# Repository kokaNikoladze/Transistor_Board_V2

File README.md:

MIDI-CONTROLLED TRANSISTOR DRIVER
---------------------------------

This Arduino sketch turns MIDI messages into PWM voltage outputs to control transistors,
analog circuits, or other devices via 8 digital pins (pins 4–11).

FEATURES:
- Responds to USB MIDI Note On/Off: 
  - Note velocity controls output voltage (0–16383).
- Control Change (CC) support:
  - Channel 2: 7-bit control (0–127), scaled to 14-bit PWM.
  - Channel 1: High-resolution 14-bit NRPN-style control with exponential response.
    (MSB on CC < 64, LSB on CC >= 64)

PIN ASSIGNMENTS:
- Outputs 1–8 → Digital pins 4–11

NRPN FORMAT (FOR CHANNEL 1 HIGH-RES CONTROL):
- Input value: 0–16383
- MSB = value / 128     → Send to control #1 (or any CC < 64)
- LSB = value % 128     → Send to control #65 (or any CC >= 64)
- IMPORTANT: Send LSB first, then MSB

OTHER NOTES:
- Uses 14-bit PWM resolution
- PWM frequency set on pin 1 to 18.384kHz
- Includes exponential curve: pow(result / 16383.0, 3)
- Built for Teensy or other boards with analogWriteResolution()

DEPENDENCIES:
- usbMIDI library (Teensy compatible)

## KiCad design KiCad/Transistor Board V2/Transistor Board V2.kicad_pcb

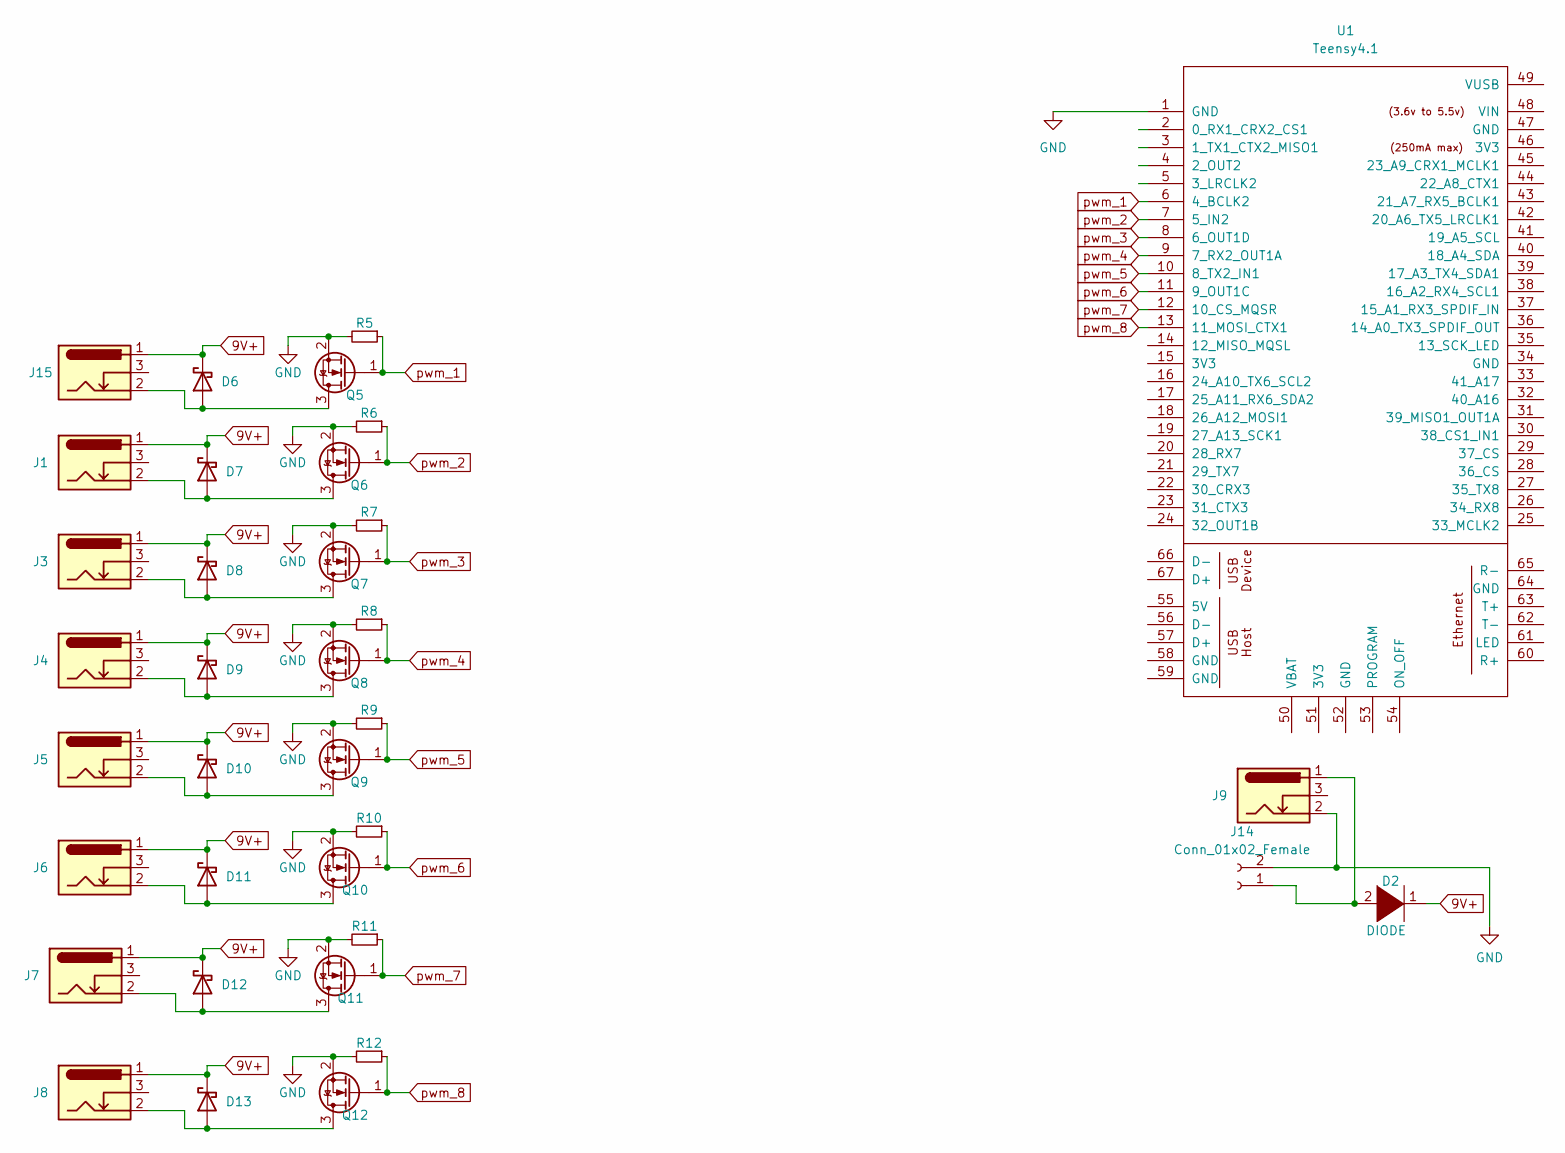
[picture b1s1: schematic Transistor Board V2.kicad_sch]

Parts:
D2: DIODE; TO-220-2_Horizontal_TabDown
D6, D7, D8, D9, D10, D11, D12, D13: SS54; D_SMA; LCSC C22452
J1, J3, J4, J5, J6, J7, J8, J9, J15: Barrel_Jack_Switch; DC-005-5A-2.0-SMT; LCSC C319134
J14: Conn_01x02_Female; PinHeader_1x02_P2.54mm_Vertical
Q5, Q6, Q7, Q8, Q9, Q10, Q11, Q12: AO3400A; SOT-23; LCSC C20917
R5, R6, R7, R8, R9, R10, R11, R12: R_Small; R_0805_2012Metric; LCSC C17414
U1: Teensy4.1; Teensy41

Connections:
9V+: D2.1 (K), D6.1 (K), D7.1 (K), D8.1 (K), D9.1 (K), D10.1 (K), D11.1 (K), D12.1 (K), D13.1 (K), J1.1, J3.1, J4.1, J5.1, J6.1, J7.1, J8.1, J15.1
GND: J9.2, J14.2, Q5.2 (S), Q6.2 (S), Q7.2 (S), Q8.2 (S), Q9.2 (S), Q10.2 (S), Q11.2 (S), Q12.2 (S), R5.2, R6.2, R7.2, R8.2, R9.2, R10.2, R11.2, R12.2, U1.1 (GND)
unnamed: D2.2 (A), J9.1, J14.1
unnamed: D6.2 (A), J15.2, Q5.3 (D)
unnamed: D7.2 (A), J1.2, Q6.3 (D)
unnamed: D8.2 (A), J3.2, Q7.3 (D)
unnamed: D9.2 (A), J4.2, Q8.3 (D)
unnamed: D10.2 (A), J5.2, Q9.3 (D)
unnamed: D11.2 (A), J6.2, Q10.3 (D)
unnamed: D12.2 (A), J7.2, Q11.3 (D)
unnamed: D13.2 (A), J8.2, Q12.3 (D)
pwm_1: Q5.1 (G), R5.1, U1.6 (4_BCLK2)
pwm_2: Q6.1 (G), R6.1, U1.7 (5_IN2)
pwm_3: Q7.1 (G), R7.1, U1.8 (6_OUT1D)
pwm_4: Q8.1 (G), R8.1, U1.9 (7_RX2_OUT1A)
pwm_5: Q9.1 (G), R9.1, U1.10 (8_TX2_IN1)
pwm_6: Q10.1 (G), R10.1, U1.11 (9_OUT1C)
pwm_7: Q11.1 (G), R11.1, U1.12 (10_CS_MQSR)
pwm_8: Q12.1 (G), R12.1, U1.13 (11_MOSI_CTX1)
pwm_9: U1.14 (12_MISO_MQSL)

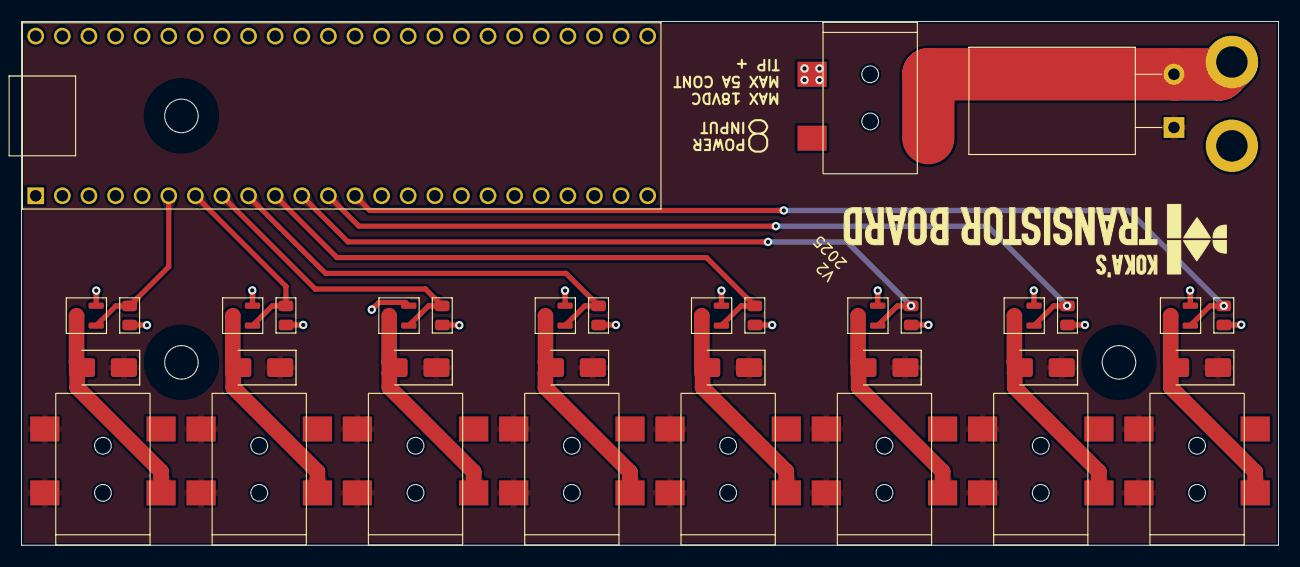
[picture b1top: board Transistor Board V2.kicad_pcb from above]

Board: 2 copper layers, 120.0 x 50.0 mm, 36 parts (0 on the bottom side), 19 nets.

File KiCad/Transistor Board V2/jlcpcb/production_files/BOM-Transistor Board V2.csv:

Comment,Designator,Footprint,LCSC,Quantity
R_Small,"R10,R11,R12,R5,R6,R7,R8,R9",R_0805_2012Metric,C17414,8
AO3400A,"Q10,Q11,Q12,Q5,Q6,Q7,Q8,Q9",SOT-23,C20917,8
SS54,"D10,D11,D12,D13,D6,D7,D8,D9",D_SMA,C22452,8
Barrel_Jack_Switch,"J1,J15,J3,J4,J5,J6,J7,J8,J9",DC-005-5A-2.0-SMT,C319134,9
DIODE,D2,TO-220-2_Horizontal_TabDown,,1
Conn_01x02_Female,J14,PinHeader_1x02_P2.54mm_Vertical,,1
Teensy4.1,U1,Teensy41,,1
